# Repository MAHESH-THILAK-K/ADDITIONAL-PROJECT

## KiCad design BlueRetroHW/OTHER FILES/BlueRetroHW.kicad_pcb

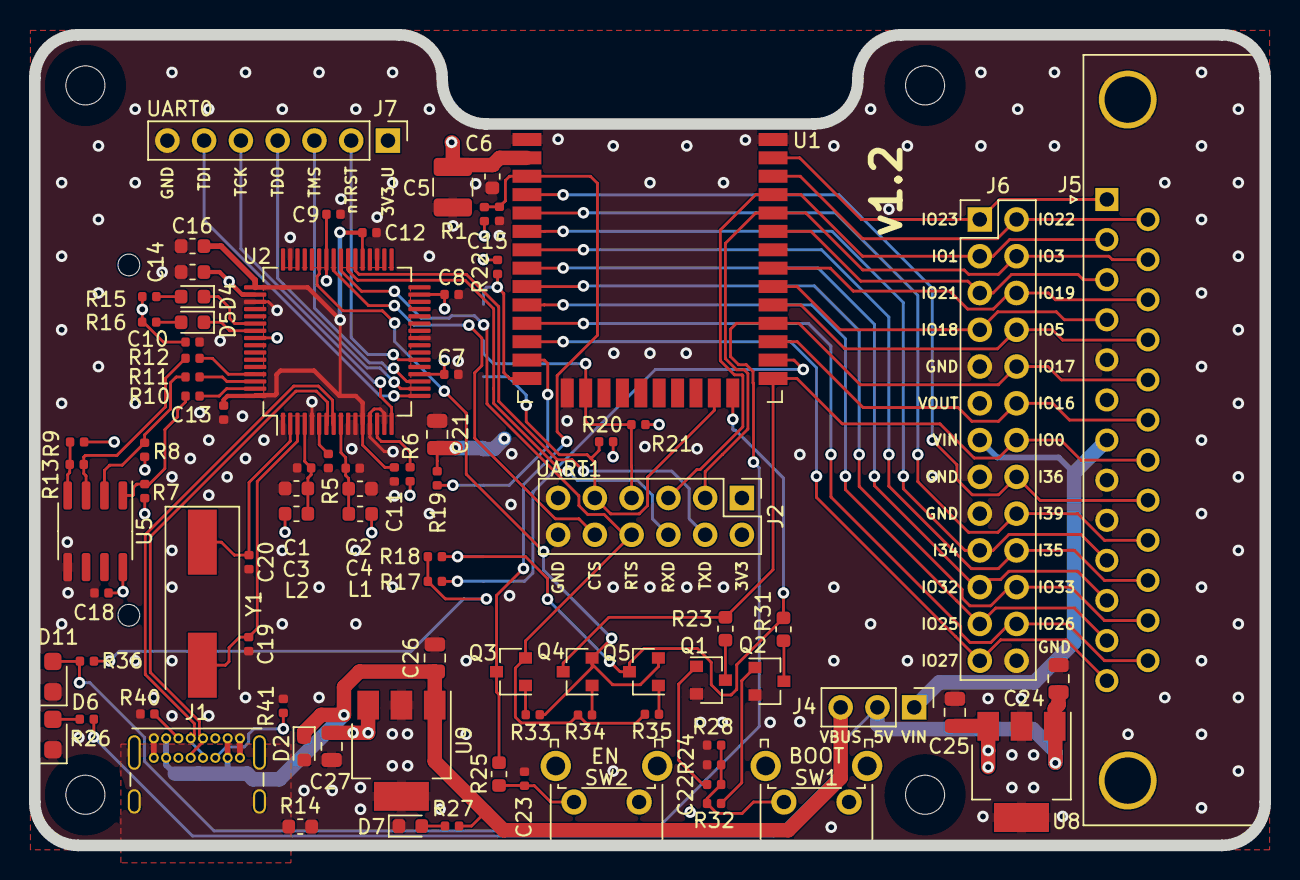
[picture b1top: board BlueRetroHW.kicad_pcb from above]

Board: 4 copper layers, 85.0 x 56.0 mm, 91 parts (1 on the bottom side), 77 nets.

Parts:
C1, C2, C7, C8, C9, C10, C11, C12, C13, C15, C18: 0.1u; C_0402_1005Metric
C3, C4, C14, C16: 4.7u; C_0603_1608Metric
C5: 100u; C_1210_3225Metric
C6: 1u; C_0603_1608Metric
C19, C20: 27p; C_0402_1005Metric
C21, C24, C25, C26, C27: 10u; C_0805_2012Metric
C22, C23: 1000p; C_0402_1005Metric
D2: ESDA25P35-1U1M; D_0603_1608Metric
D4: GREEN; LED_0603_1608Metric
D5, D7: RED; LED_0603_1608Metric
D6: GREEN_RA; LED_0605_1611Metric
D11: RED_RA; LED_0605_1611Metric
H1, H2, H3, H4: MountingHole; MountingHole_2.7mm_M2.5
J1: USB_C_Receptacle_USB2.0; USB_C_Receptacle_GCT_USB4085
J2: Conn_02x06; PinHeader_2x06_P2.54mm_Vertical
J3: SD_Card; SD_Kyocera_145638009511859+
J4: Conn_01x03; PinHeader_1x03_P2.54mm_Vertical
J5: DB25_Female; DSUB-25_Female_Horizontal_P2.77x2.84mm_EdgePinOffset8.1mm_H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
J6: Conn_02x13; PinHeader_2x13_P2.54mm_Vertical_TB
J7: Conn_01x07; PinHeader_1x07_P2.54mm_Vertical
L1, L2: 1K@100MHz; L_0603_1608Metric
Q1, Q2: BSS138; SOT-23
Q3, Q4, Q5: S8050; SOT-23
R1, R5: 12K; R_0402_1005Metric
R6, R24, R32: 1K; R_0402_1005Metric
R7, R8, R9, R17, R18, R19, R20, R21, R22, R28: 10K; R_0402_1005Metric
R10, R11, R12: 33; R_0402_1005Metric
R13: 2.2K; R_0402_1005Metric
R14, R23, R25, R31: 0; R_0603_1608Metric
R15, R16, R36: 64.9; R_0402_1005Metric
R26, R27: 150; R_0402_1005Metric
R33, R34, R35: 100K; R_0402_1005Metric
R40, R41: 5.1K; R_0402_1005Metric
SW1: BOOT; SW_Tactile_SPST_Angled_PTS645Vx83-2LFS
SW2: EN; SW_Tactile_SPST_Angled_PTS645Vx83-2LFS
U1: ESP32-WROOM-32E; ESP32-WROOM-32
U2: FT2232HL; LQFP-64_10x10mm_P0.5mm
U5: M93C46; SOIC-8_3.9x4.9mm_P1.27mm
U8, U9: AP7361C-33E; SOT-223-3_TabPin2
Y1: 12MHz; Crystal_SMD_HC49-SD

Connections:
+1V8: C11.1, C12.1, C13.1, C16.1, U2.12, U2.37, U2.49, U2.64
+3V3: C5.1, C6.1, C21.1, C25.1, J2.1, J2.2, J3.4, J5.6, J6.6, R1.1, R17.1, R18.1, R19.1, R20.1, R21.1, R22.1, R36.1, SW1.1, U1.2, U8.3
+3V3_USB: C7.1, C8.1, C9.1, C10.1, C14.1, C18.1, C27.1, J7.1, L1.2, L2.2, R6.1, R7.2, R8.2, R9.2, R15.2, R16.2, U2.20, U2.31, U2.42, U2.50, U2.56, U5.8, U9.3
+5V: C24.1, J4.2, R26.1, U8.1
/EN: C15.1, Q3.3, R1.2, R25.1, U1.3
/I34: J5.10, J6.10, U1.6
/I35: J5.23, J6.23, U1.7
/I36: J5.21, J6.21, U1.4
/I39: J5.22, J6.22, U1.5
/IO0: J5.20, J6.20, Q4.3, R23.1, U1.25
/IO1: J2.5, J5.2, J6.2, U1.35
/IO2: J3.7, Q5.3, R18.2, R31.1, U1.24
/IO3: J2.3, J5.15, J6.15, U1.34
/IO4: J3.8, R17.2, U1.26
/IO5: J5.17, J6.17, U1.29
/IO12: J3.9, R22.2, U1.14
/IO13: J2.7, J3.1, R21.2, U1.16
/IO14: J3.5, R19.2, U1.13
/IO15: J2.9, J3.2, R20.2, U1.23
/IO16: J5.19, J6.19, U1.27
/IO17: D11.2, J5.18, J6.18, R36.2, U1.28
/IO18: J5.4, J6.4, U1.30
/IO19: J5.16, J6.16, U1.31
/IO21: J5.3, J6.3, U1.33
/IO22: J5.14, J6.14, U1.36
/IO23: J5.1, J6.1, U1.37
/IO25: J5.12, J6.12, U1.10
/IO26: J5.25, J6.25, U1.11
/IO27: J5.13, J6.13, U1.12
/IO32: J5.11, J6.11, U1.8
/IO33: J5.24, J6.24, U1.9
/RXD: J2.6, U2.39
/TCK: J7.5, U2.16
/TDI: J7.6, U2.17
/TDO: J7.4, U2.18
/TMS: J7.3, U2.19
/TXD: J2.4, U2.38
/USB_C_N: J1.A7, J1.B7, U2.7
/USB_C_P: J1.A6, J1.B6, U2.8
/nCTS: J2.10, U2.41
/nDTR: Q4.2, Q5.2, R33.2, U2.43
/nRTS: J2.8, Q3.2, R34.2, R35.2, U2.40
/nTRST: J7.2, U2.22
GND: C1.2, C2.2, C3.2, C4.2, C5.2, C6.2, C7.2, C8.2, C9.2, C10.2, C11.2, C12.2, C13.2, C14.2, C15.2, C16.2, C18.2, C19.2, C20.2, C21.2, C22.2, C23.2, C24.2, C25.2, C26.2, C27.2, D2.2, D6.1, D7.1, D11.1, J1.A1, J1.A12, J1.B1, J1.B12, J2.11, J2.12, J3.3, J3.6, J3.12, J3.13, J5.0, J5.5, J5.8, J5.9, J6.5, J6.8, J6.9, J6.26, J7.7, Q1.2, Q2.2, R5.1, R14.2, R28.2, R40.1, R41.1, SW2.1, U1.1, U1.15, U1.38, U2.1, U2.5, U2.10, U2.11, U2.13, U2.15, U2.25, U2.35, U2.47, U2.51, U5.5, U8.2, U9.2
unnamed: C1.1, C3.1, L2.1, U2.4
unnamed: C2.1, C4.1, L1.1, U2.9
unnamed: C19.1, U2.3, Y1.2
unnamed: C20.1, U2.2, Y1.1
unnamed: C22.1, R24.2, R28.1, R32.2, SW1.2
unnamed: C23.1, R25.2, SW2.2
unnamed: D4.1, U2.54
unnamed: D4.2, R15.1
unnamed: D5.1, U2.55
unnamed: D5.2, R16.1
unnamed: D6.2, R26.2
unnamed: D7.2, R27.2
unnamed: J1.A5, R40.2
unnamed: J1.B5, R41.2
unnamed: J1.S1, R14.1
unnamed: Q1.1, R24.1
unnamed: Q1.3, R23.2
unnamed: Q2.1, R32.1
unnamed: Q2.3, R31.2
unnamed: Q3.1, R33.1
unnamed: Q4.1, R34.1
unnamed: Q5.1, R35.1
unnamed: R5.2, U2.6
unnamed: R6.2, U2.14
unnamed: R7.1, R10.1, U5.1
unnamed: R10.2, U2.63
unnamed: R8.1, R11.1, U5.2
unnamed: R11.2, U2.62
unnamed: R12.1, R13.2, U5.3
unnamed: R12.2, U2.61
unnamed: R9.1, R13.1, U5.4
VBUS: C26.1, D2.1, J1.A4, J1.A9, J1.B4, J1.B9, J4.3, R27.1, U9.1
VIN: J4.1, J5.7, J6.7

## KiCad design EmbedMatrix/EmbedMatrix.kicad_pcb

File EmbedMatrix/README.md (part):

<div align="center">

<br/>

```
███████╗███╗   ███╗██████╗ ███████╗██████╗ ███╗   ███╗ █████╗ ████████╗██████╗ ██╗██╗  ██╗
██╔════╝████╗ ████║██╔══██╗██╔════╝██╔══██╗████╗ ████║██╔══██╗╚══██╔══╝██╔══██╗██║╚██╗██╔╝
█████╗  ██╔████╔██║██████╔╝█████╗  ██║  ██║██╔████╔██║███████║   ██║   ██████╔╝██║ ╚███╔╝ 
██╔══╝  ██║╚██╔╝██║██╔══██╗██╔══╝  ██║  ██║██║╚██╔╝██║██╔══██║   ██║   ██╔══██╗██║ ██╔██╗ 
███████╗██║ ╚═╝ ██║██████╔╝███████╗██████╔╝██║ ╚═╝ ██║██║  ██║   ██║   ██║  ██║██║██╔╝ ██╗
╚══════╝╚═╝     ╚═╝╚═════╝ ╚══════╝╚═════╝ ╚═╝     ╚═╝╚═╝  ╚═╝   ╚═╝   ╚═╝  ╚═╝╚═╝╚═╝  ╚═╝
```

<h3>🔗 Modular Embedded Matrix Platform for Multi-Node Sensing & Control</h3>
<h4><i>Connect everything. Scale infinitely. Deploy anywhere.</i></h4>

<br/>

<br/>

---

**[📡 Overview](#-overview) · [✨ Features](#-features) · [🔩 Architecture](#-system-architecture) · [📐 Matrix Topology](#-matrix-topology) · [📦 BOM](#-bill-of-materials) · [🚀 Quickstart](#-quickstart) · [📁 File Tree](#-file-tree) · [🗺 Roadmap](#-roadmap) · [🤝 Contribute](#-contributing)**

---

</div>

<br/>

## 📡 Overview

**EmbedMatrix** is a scalable, modular embedded matrix platform designed for distributed sensing, multi-node control, and mesh-capable IoT deployments. Built around the **STM32F031K6T6** ARM Cortex-M0+ MCU, each EmbedMatrix node is a self-contained, hot-swappable unit that snaps into a shared backplane bus — enabling you to build sensor grids, actuator arrays, and telemetry networks from 1 node to 64 nodes without redesigning hardware.

Every node carries its own processing, communication, and power regulation, while the backplane provides a unified interconnect mesh of **I²C, SPI, and UART** buses with automatic address arbitration. Whether you're building a 4-node motor controller, a 16-node environmental sensor grid, or a 64-node LED matrix display, EmbedMatrix scales linearly — just add nodes.

```
EmbedMatrix Design Philosophy
───────────────────────────────────
  → Hot-swappable node architecture      (snap-in / snap-out, no reboot)
  → Unified backplane bus matrix         (I²C + SPI + UART shared lanes)
  → Auto-address arbitration             (DIP switch / EEPROM ID per node)
  → Self-contained per-node power        (LDO + ferrite, no bus droop)
  → Crystal-locked sync across nodes     (HSE 8 MHz, PLL 48 MHz)
  → ESD-protected edge connectors        (TVS diodes on all bus lines)
  → Fabrication-ready from day one       (JLCPCB / PCBWay Gerber-clean)
```

<br/>

---

## ✨ Features

<br/>

<table>
<tr>
<td width="50%">

### 🔗 Matrix & Bus Architecture
- **Hot-swappable node slots** — add/remove nodes live, no system reset
- **Unified backplane bus** — I²C (400 kHz), SPI (24 Mbit/s), UART (115200) shared
- **Auto-address arbitration** — 6-bit DIP switch or EEPROM-stored node ID
- **Bus isolation per node** — PCA9548 I²C mux + SPI chip-select matrix
- **ESD protection** — TVS diode arrays on all backplane edge connectors
- **Status LED matrix** — per-node RGB status, backplane health indicator

</td>
<td width="50%">

### 🧠 Processing & Control
- **ARM Cortex-M0+** @ 48 MHz per node (0.95 DMIPS/MHz)
- **32 KB Flash** — distributed firmware, mesh protocol stack
- **4 KB SRAM** — runtime buffers, bus arbitration tables
- **12-bit ADC** — 10 channels per node for sensor aggregation
- **9-channel PWM** — synchronized motor / LED / servo control
- **Hardware multiplier** — single-cycle 32×32 MAC for DSP tasks

</td>
</tr>
<tr>
<td width="50%">

### ⚡ Power & Reliability
- **Per-node LDO 3.3V** — AMS1117-3.3 with ferrite bead isolation
- **Bulk capacitor reservoir** — 10µF per node, 100µF on backplane
- **Brown-out reset (BOR)** — per-node voltage monitoring
- **Independent watchdog (IWDG)** — node-level crash recovery
- **Low-power modes** — Sleep, Stop, Standby (< 10 µA standby)

</td>
<td width="50%">

### 📡 Communication & Sync
- **USART1** — inter-node messaging, debug console, AT commands
- **SPI1** — high-speed sensor / flash / display peripheral bus
- **I²C1** — multi-drop sensor network, EEPROM config storage
- **SWD debug** — 2-wire programming per node via backplane
- **Sync line** — dedicated hardware sync for PWM phase-lock across nodes

</td>
</tr>
</table>

<br/>

---

## 🔩 System Architecture

```
╔═══════════════════════════════════════════════════════════════════════════╗
║                    EmbedMatrix — Full System Block Diagram               ║
╠═══════════════════════════════════════════════════════════════════════════╣
║                                                                           ║
║   ══════════════════════════ Backplane Bus Matrix ══════════════════════  ║
║                                                                           ║
║   ┌─────────────────────────────────────────────────────────────────────┐ ║
║   │  BUS_I²C_SCL  │  BUS_I²C_SDA  │  BUS_SPI_SCK  │  BUS_SPI_MOSI    │ ║
║   │  BUS_SPI_MISO │  BUS_UART_TX  │  BUS_UART_RX  │  BUS_SYNC_CLK    │ ║
║   │  BUS_VCC_3V3  │  BUS_VCC_5V   │  BUS_GND      │  BUS_NRST_MATRIX │ ║
║   └─────────────────────────────────────────────────────────────────────┘ ║
║                                    │                                      ║
║         ┌──────────┬──────────┬────┴────┬──────────┬──────────┐           ║
║         ▼          ▼          ▼         ▼          ▼          ▼           ║
║   ┌─────────┐ ┌─────────┐ ┌─────────┐ ┌─────────┐ ┌─────────┐ ┌─────────┐║
║   │ Node 00 │ │ Node 01 │ │ Node 02 │ │ Node 03 │ │  ...    │ │ Node 63 │║
║   │ ID=0x00 │ │ ID=0x01 │ │ ID=0x02 │ │ ID=0x03 │ │         │ │ ID=0x3F │║
║   └────┬────┘ └────┬────┘ └────┬────┘ └────┬────┘ └────┬────┘ └────┬────┘║
║        │           │           │           │           │           │      ║
║   ═════╧═══════════╧═══════════╧═══════════╧═══════════╧═══════════╧════  ║
║                                                                           ║
║   ════════════════════════ Single Node Internals ═══════════════════════  ║
║                                                                           ║
║   ┌─────────────────────────────────────────────────────────────────┐    ║
║   │              STM32F031K6T6 — ARM Cortex-M0+ Core               │    ║
║   │                                                                 │    ║
║   │   ┌─────────────┐  ┌─────────────┐  ┌─────────────────────┐   │    ║
║   │   │  32 KB Flash │  │   4 KB SRAM  │  │  NVIC + SysTick     │   │    ║
║   │   │  (0x08000000)│  │  (0x20000000)│  │  32 IRQ priorities  │   │    ║
║   │   └─────────────┘  └─────────────┘  └─────────────────────┘   │    ║
║   │                                                                 │    ║
║   │   ┌─────────────┐  ┌─────────────┐  ┌─────────────────────┐   │    ║
║   │   │   RCC/PLL   │  │    PWR/BOR   │  │   Bus Arbiter (SW)  │   │    ║
║   │   │  48 MHz SYS │  │   LDO 1.8V   │  │   Node ID register  │   │    ║
║   │   └─────────────┘  └─────────────┘  └─────────────────────┘   │    ║
║   └────────────────────────┬──────────────────────────────────────┘    ║
║                            │                                           ║
║   ════════════════════════ Peripherals ═══════════════════════════════  ║
║                            │                                           ║
║   ┌──────────┐ ┌──────────┐ ┌──────────┐ ┌──────────┐ ┌──────────┐   ║
║   │  USART1  │ │  SPI1    │ │  I²C1    │ │  TIM1/2  │ │  ADC1    │   ║
║   │ PA9/PA10 │ │ PA5-PA7  │ │ PA9/PA10 │ │ PA0-PA3  │ │ PA0-PA7  │   ║
║   │ 115200   │ │ 24 Mbit  │ │ 400 kHz  │ │  PWM     │ │ 12-bit   │   ║
║   └──────────┘ └──────────┘ └──────────┘ └──────────┘ └──────────┘   ║
║                            │                                           ║
║   ════════════════════════ Node Interface ══════════════════════════  ║
║                            │                                           ║
║        ┌───────────────────┴───────────────────┐                       ║
║        ▼                                       ▼                       ║
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
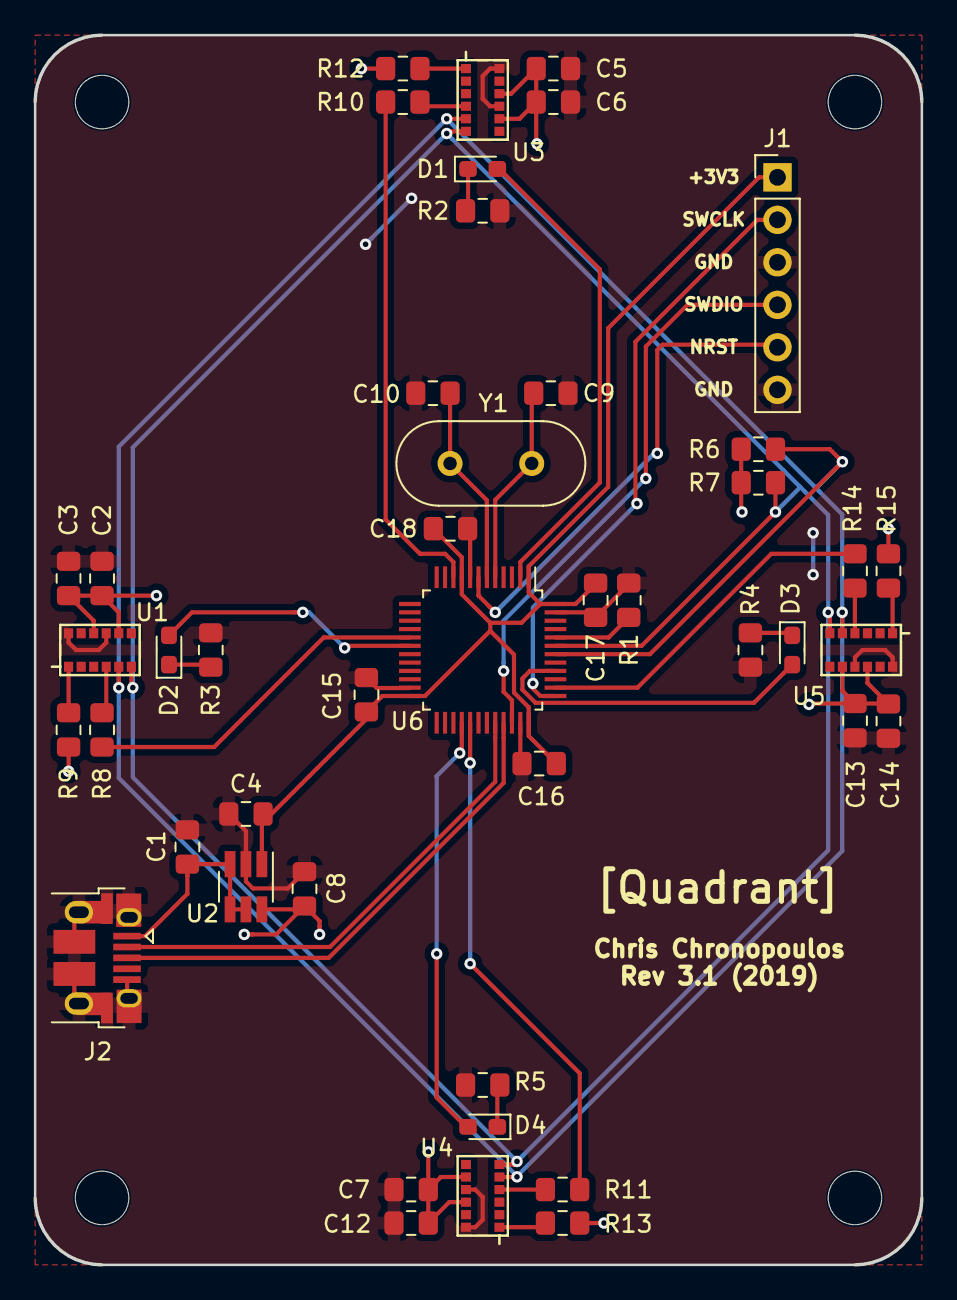
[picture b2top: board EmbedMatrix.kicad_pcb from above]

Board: 2 copper layers, 53.0 x 73.5 mm, 45 parts (0 on the bottom side), 34 nets.

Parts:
C1, C4, C8: 1uF; C_0805_2012Metric_Pad1.15x1.40mm_HandSolder
C2, C5, C7, C13: 4.7uF; C_0805_2012Metric_Pad1.15x1.40mm_HandSolder
C3, C6, C12, C14: 0.1uF; C_0805_2012Metric_Pad1.15x1.40mm_HandSolder
C9, C10: 18 pF; C_0805_2012Metric_Pad1.15x1.40mm_HandSolder
C15, C16, C17, C18: 0.1 uF; C_0805_2012Metric_Pad1.15x1.40mm_HandSolder
D1, D2, D3, D4: LED; LED_0603_1608Metric_Pad1.05x0.95mm_HandSolder
J1: Conn_01x06; PinHeader_1x06_P2.54mm_Vertical
J2: USB_B_Micro; USB_Micro-B_Amphenol_10103594-0001LF_Horizontal
R1: 10k; R_0805_2012Metric_Pad1.15x1.40mm_HandSolder
R2, R3, R4, R5: 10; R_0805_2012Metric_Pad1.15x1.40mm_HandSolder
R6, R7: 4.7k; R_0805_2012Metric_Pad1.15x1.40mm_HandSolder
R8, R9, R10, R11, R12, R13, R14, R15: 47k; R_0805_2012Metric_Pad1.15x1.40mm_HandSolder
U1, U3, U4, U5: VL6180X
U2: AP7332-2833; SOT-23-6_Handsoldering
U6: STM32F070CBTx; LQFP-48_7x7mm_P0.5mm
Y1: 8 MHz; Crystal_HC49-U_Vertical

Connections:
+2V8: C2.2, C3.2, C5.2, C6.2, C7.2, C8.1, C12.2, C13.2, C14.2, R6.1, R7.1, R9.1, R12.1, R13.1, R15.1, U1.8, U1.10, U2.6, U3.8, U3.10, U4.8, U4.10, U5.8, U5.10
+3V3: C4.1, C15.2, C16.2, C17.2, C18.2, J1.1, U2.1, U6.1, U6.9, U6.24, U6.36, U6.48
EN1: R10.1, U6.10
EN2: R14.1, U6.38
EN3: R11.1, U6.29
EN4: R8.1, U6.17
GND: C1.2, C2.1, C3.1, C4.2, C5.1, C6.1, C7.1, C8.2, C9.2, C10.2, C12.1, C13.1, C14.1, C15.1, C16.1, C17.1, C18.1, J1.3, J1.6, J2.5, J2.6, R1.1, R2.1, R3.1, R4.1, R5.1, U1.9, U1.12, U2.2, U3.9, U3.12, U4.9, U4.12, U5.9, U5.12, U6.8, U6.23, U6.35, U6.47
NRST: J1.5, U6.7
unnamed: C9.1, U6.5, Y1.1
unnamed: C10.1, U6.6, Y1.2
unnamed: D1.1, R2.2
unnamed: D1.2, U6.2
unnamed: D2.1, R3.2
unnamed: D2.2, U6.18
unnamed: D3.1, R4.2
unnamed: D3.2, U6.40
unnamed: D4.1, R5.2
unnamed: D4.2, U6.28
unnamed: R1.2, U6.44
unnamed: R8.2, U1.4
unnamed: R9.2, U1.1
unnamed: R10.2, U3.4
unnamed: R11.2, U4.4
unnamed: R12.2, U3.1
unnamed: R13.2, U4.1
unnamed: R14.2, U5.4
unnamed: R15.2, U5.1
SCL: R6.2, U1.5, U3.5, U4.5, U5.5, U6.42
SDA: R7.2, U1.6, U3.6, U4.6, U5.6, U6.43
SWCLK: J1.2, U6.37
SWDIO: J1.4, U6.34
USB5V: C1.1, J2.1, U2.3, U2.4, U2.5
USBDM: J2.2, U6.32
USBDP: J2.3, U6.33

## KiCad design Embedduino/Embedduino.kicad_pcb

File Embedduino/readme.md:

# 🚀 Embedduino

> ⚡ Compact Arduino-compatible SMD development board for embedded systems & IoT.

---

## 📌 About

**Embedduino** is a custom-designed development board based on the **ATmega328P-AU**, integrating power regulation, communication interfaces, and onboard peripherals into a compact PCB.

It is built to bridge the gap between **Arduino prototyping and real hardware design**.

---

## ✨ Features

* ATmega328P-AU (Arduino UNO compatible)
* 16 MHz Crystal Oscillator
* USB Type-C (5V input)
* 12V Barrel Jack support
* Dual LDO (12V → 5V → 3.3V)
* Bluetooth support (HC-05 / HC-06)
* RGB LED + Status LEDs
* Onboard Buzzer
* ICSP Programming Header
* Full GPIO breakout (D0–D13, A0–A5)

---

## 🧩 Components

| Component     | Description               |
| ------------- | ------------------------- |
| ATmega328P-AU | Microcontroller           |
| TLV76750      | 12V → 5V Regulator        |
| AMS1117-3.3V  | 5V → 3.3V Regulator       |
| WS2812B       | Addressable RGB LED       |
| HC-05         | Bluetooth Module          |
| APDS-9960     | Gesture Sensor (optional) |
| USB-C         | Power Input               |
| Barrel Jack   | 12V Input                 |
| ICSP          | Programming Header        |
| Buzzer        | Audio Output              |

---

## ⚙️ Specifications

* **MCU:** ATmega328P-AU
* **Clock:** 16 MHz
* **Voltage:** 5V / 12V
* **Logic Levels:** 5V / 3.3V
* **Communication:** UART
* **PCB:** 2 Layer

---

## 🚀 Getting Started

**Bootloader**

* Flash using ICSP programmer

**Upload Code**

* Use FTDI / USB-UART
* Select **Arduino UNO** in Arduino IDE

**Power Options**

* USB-C (5V)
* Barrel Jack (12V)

---

## 🔌 Pinout

| Type    | Pins            |
| ------- | --------------- |
| Digital | D0–D13          |
| Analog  | A0–A5           |
| UART    | TX / RX         |
| Power   | 5V / 3.3V / GND |

---

## ⚠️ Note

> DRC is not fully resolved — verify before fabrication.

---
## 🧪 Use Cases

* Robotics
* IoT Projects
* Wireless Systems
* Embedded Learning

---

## 🛠️ Roadmap

* [ ] Fix DRC issues
* [ ] Add USB-UART IC
* [ ] Improve power efficiency
* [ ] Hardware testing

---

## 👨‍💻 Author

**Mahesh Thilak**
🔗 https://github.com/MAATHES-THILAK-K

---

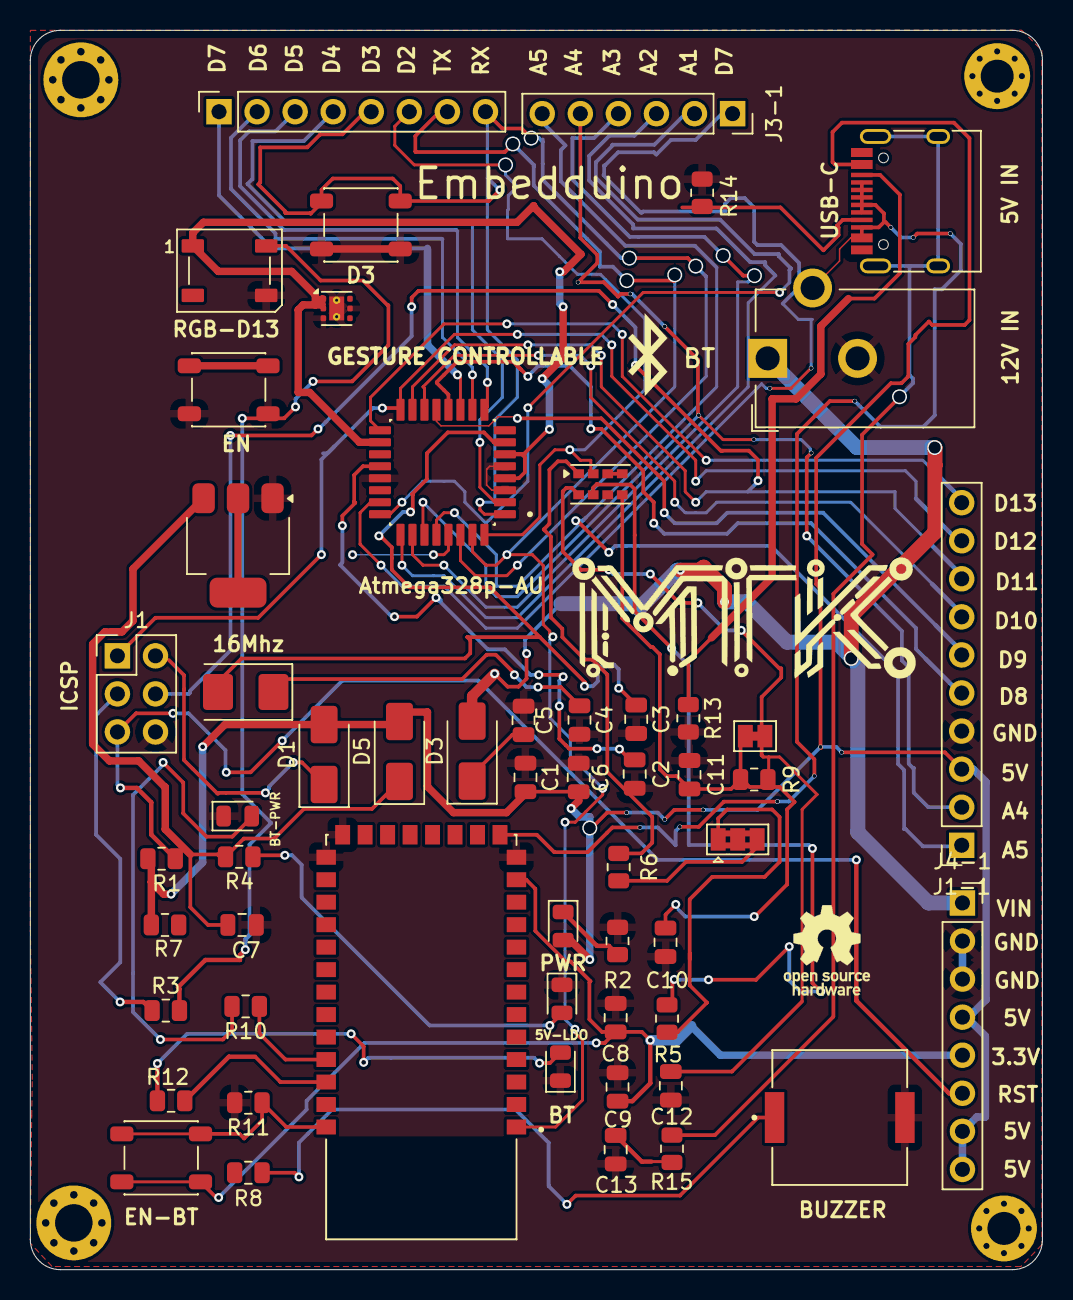
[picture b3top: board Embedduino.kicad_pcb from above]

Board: 2 copper layers, 67.5 x 82.7 mm, 57 parts (0 on the bottom side), 51 nets.

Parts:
5V-LDO: LED; LED_0805_2012Metric
12V IN: Barrel_Jack; BarrelJack_CUI_PJ-102AH_Horizontal
16Mhz: Crystal; Crystal_SMD_5032-2Pin_5.0x3.2mm
BT: LED; LED_0805_2012Metric
BT-PWR: LED; LED_0805_2012Metric
BZ1: Buzzer; SPKR_PKMCS0909E4000-R1
C1, C2, C13: 100nf; C_0805_2012Metric
C3, C4: 22pf; C_0805_2012Metric
C5: 1uf; C_0805_2012Metric
C6: 2.2uf; C_0805_2012Metric
C7, C8: 10uf; C_0805_2012Metric
C9: 0.1uf; C_0805_2012Metric
C10: 1.0uf; C_0805_2012Metric
C11: 100uf; C_0805_2012Metric
C12: 1.0fu; C_0805_2012Metric
D1, D3#2, D5: SS14; D_SMA
D3: SW_DPST_x2; SW_SPST_PTS647_Sx50
EN: SW_DPST_x2; SW_SPST_PTS647_Sx50
EN-BT: SW_DPST_x2; SW_SPST_PTS647_Sx50
H1, H2: MountingHole; MountingHole_2.2mm_M2_Pad_Via
J1: ICSP; PinHeader_2x03_P2.54mm_Vertical
J1-1: Conn_01x10_Pin; PinSocket_1x10_P2.54mm_Vertical
J2-1, J4-1: Conn_01x08_Pin; PinSocket_1x08_P2.54mm_Vertical
J3-1: Conn_01x06_Pin; PinSocket_1x06_P2.54mm_Vertical
JP1: SolderJumper_3_Bridged123; SolderJumper-3_P1.3mm_Bridged2Bar123_Pad1.0x1.5mm
JP2: SolderJumper_2_Bridged; SolderJumper-2_P1.3mm_Bridged_Pad1.0x1.5mm
PWR: LED; LED_0805_2012Metric
R1, R7, R11: 10k; R_0805_2012Metric
R2, R12: 1k; R_0805_2012Metric
R3: 330; R_0805_2012Metric
R4: 2.2k; R_0805_2012Metric
R5, R6: 4.7k; R_0805_2012Metric
R8: 100; R_0805_2012Metric
R9: DNP; R_0805_2012Metric
R10: 2k; R_0805_2012Metric
R13, R14: 5.1k; R_0805_2012Metric
R15: 1M; R_0805_2012Metric
RGB-D13: WS2812B; LED_WS2812B_PLCC4_5.0x5.0mm_P3.2mm
U1: ATMEGA328P-AU; QFP80P900X900X120-32N
U2: TLV76750DRVx; WSON-6-1EP_2x2mm_P0.65mm_EP1x1.6mm_ThermalVias
U3: AMS1117-3.3; SOT-223-3_TabPin2
U4: APDS-9960; Avago_APDS-9960
U5: HC-05; XCVR_HC-05
USB-C: USB_C_Receptacle_PowerOnly_6P; USB_C_Receptacle_HRO_TYPE-C-31-M-12

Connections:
3.3v: C8.1, C9.1, EN-BT.2 (B), J4-1.5, U3.2 (VO), U5.12 (3.3_VCC)
5V: C1.2, C6.1, D1.2 (A), D5.2 (A), J1-1.3, J4-1.4, J4-1.7, J4-1.8, PWR.2 (A), R1.2, R7.1, RGB-D13.1 (VDD), U1.4 (VCC), U1.6 (VCC__1), U1.18 (AVCC), U2.1 (OUT), U2.2 (SNS), USB-C.A9 (VBUS), USB-C.B9 (VBUS)
A0: J3-1.1, U1.23 (PC0)
A1: J3-1.2, U1.24 (PC1)
A2: J3-1.3, U1.25 (PC2)
A3: J3-1.4, U1.26 (PC3)
A4: J1-1.2, J3-1.5, U1.27 (PC4)
A5: J1-1.1, J3-1.6, U1.28 (PC5)
D2: J2-1.6, R7.2, U1.32 (PD2), U4.2 (INT)
D3: D3.1 (A), J2-1.5, U1.1 (PD3)
D4: J2-1.4, U1.2 (PD4)
D5: J2-1.3, U1.9 (PD5)
D6: J2-1.2, R8.1, U1.10 (PD6)
D7: J2-1.1, U1.11 (PD7)
D8: J1-1.5, U1.12 (PB0)
D9: J1-1.6, U1.13 (PB1)
D10: J1-1.7, U1.14 (PB2)
D11: J1.4, J1-1.8, U1.15 (PB3)
D12: J1.1, J1-1.9, U1.16 (PB4)
D13: J1.3, J1-1.10, R3.1, U1.17 (PB5)
GND: 5V-LDO.1 (K), 12V IN.2, BT.1 (K), BT-PWR.1 (K), BZ1.2 (-), C1.1, C2.2, C3.2, C4.2, C5.2, C6.2, C7.2, C8.2, C9.2, C10.1, C11.2, C12.2, C13.2, D3.2 (B), EN.2 (B), J1.6, J1-1.4, J4-1.2, J4-1.3, R2.1, R11.2, R13.2, R14.2, RGB-D13.3 (VSS), U1.3 (GND), U1.5 (GND__1), U1.21 (GND__2), U2.3 (GND), U2.5 (GND), U2.7 (PAD), U3.1 (GND), U4.6 (GND), U5.13 (GND), U5.21 (GND), U5.22 (GND), USB-C.A12 (GND), USB-C.B12 (GND)
unnamed: BZ1.1 (+), R8.2
unnamed: C13.1, R15.2
unnamed: D1.1 (K), J1.2
unnamed: PWR.1 (K), R2.2
unnamed: C5.1, D3#2.1 (K), U2.4 (EN), U2.6 (IN)
unnamed: R3.2, RGB-D13.4 (DIN)
unnamed: C7.1, D5.1 (K), R4.1, U3.3 (VI)
unnamed: 5V-LDO.2 (A), R4.2
unnamed: BT-PWR.2 (A), R10.2
unnamed: BT.2 (A), R12.1
unnamed: R14.1, USB-C.A5 (CC1)
unnamed: R13.1, USB-C.B5 (CC2)
unnamed: R15.1, USB-C.S1 (SHIELD)
unnamed: JP1.1 (A), R5.1
unnamed: JP1.3 (B), R6.1
unnamed: C12.1, JP2.2 (B), R9.1, U4.8 (VDD)
unnamed: EN-BT.1 (A), R11.1, U5.34 (PIO[11])
unnamed: C2.1, U1.20 (AREF)
unnamed: U4.3 (LDR), U4.4 (LED_K)
unnamed: R10.1, U5.31 (PIO[8])
PB6: 16Mhz.2, C3.1, U1.7 (PB6)
PB7: 16Mhz.1, C4.1, U1.8 (PB7)
RST: EN.1 (A), J1.5, J4-1.6, R1.1, U1.29 (PC6/~RESET)
RX: J2-1.8, U1.30 (PD0), U5.2 (UART-RX)
SCL: R5.2, U4.7 (SCL)
SDA: R6.2, U4.1 (SDA)
STATE: R12.2, U5.32 (PIO[9])
TX: J2-1.7, U1.31 (PD1), U5.1 (UART-TX)
Vin: 12V IN.1, D3#2.2 (A), J4-1.1
Vl: C10.2, C11.1, JP2.1 (A), R9.2, U4.5 (LED_A)

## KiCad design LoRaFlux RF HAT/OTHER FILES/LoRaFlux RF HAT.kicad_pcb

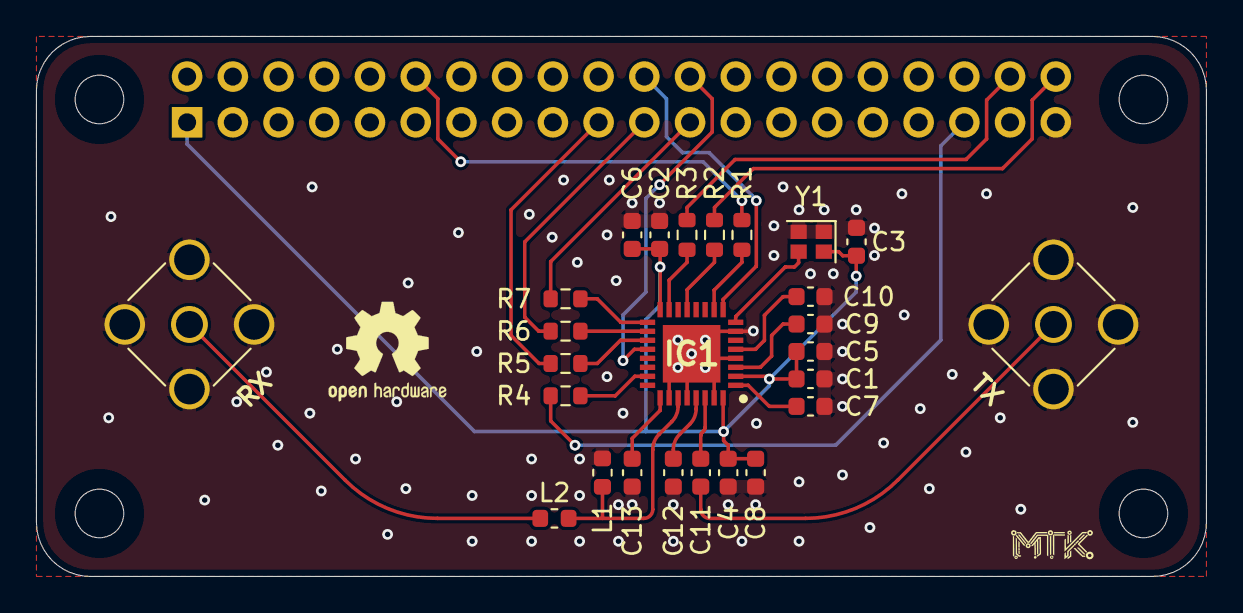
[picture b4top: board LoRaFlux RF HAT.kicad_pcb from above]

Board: 2 copper layers, 65.0 x 30.0 mm, 32 parts (1 on the bottom side), 28 nets.

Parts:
C1, C2, C3, C4: 10n; C_0603_1608Metric
C5, C6, C7, C8, C9, C10, C13: 100n; C_0603_1608Metric
C11: 33p; C_0603_1608Metric
C12: 27p; C_0603_1608Metric
H1, H2, H3, H4: MountingHole; MountingHole_2.7mm_M2.5_DIN965
IC1: SX1255; QFN50P500X500X80-33N-D
J1: TX_SMA; SMA_Amphenol_901-144_Vertical
J2: RX_SMA; SMA_Amphenol_901-144_Vertical
J3: RPi Zero; PinSocket_2x20_P2.54mm_Vertical
L1: 82n; L_0603_1608Metric
L2: 39n; L_0603_1608Metric
R1, R2, R3, R4, R5, R6, R7: 100R; R_0603_1608Metric
SYM1: Logo_Open_Hardware_Small; OSHW-Logo2_7.3x6mm_SilkScreen
Y1: 32MHz; Crystal_SMD_2016-4Pin_2.0x1.6mm

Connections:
+3V3: C1.1, C2.1, C3.1, C4.1, C5.1, C6.1, C8.1, IC1.2 (VBATI), IC1.16 (VBAT2), IC1.32 (VBAT3), J3.1, Y1.4 (VDD)
/DIO2: J3.35, R4.1
/I_IN: J3.40, R2.2
/I_OUT: J3.38, R3.2
/MISO: J3.21, R6.1
/MOSI: J3.19, R5.1
/OUT: J3.12, R1.2
/RST: IC1.9 (RESET), J3.22
/SCK: J3.23, R7.1
/TCXO_CLK: IC1.8 (XTB), Y1.3 (OUT)
/~CS: IC1.20 (NSS), J3.24
GND: C1.2, C2.2, C3.2, C4.2, C5.2, C6.2, C7.2, C8.2, C9.2, C10.2, C12.2, C13.2, IC1.4 (GND_1), IC1.7 (GND_2), IC1.26 (GND_3), IC1.28 (GND_4), IC1.31 (GND_5), IC1.33 (GND_6), J1.2 (Ext), J2.2 (Ext), J3.39, L1.1, Y1.1 (Tri-State), Y1.2 (GND)
unnamed: IC1.10 (CK_OUT), R1.1
unnamed: IC1.23 (DIO2), R4.2
unnamed: IC1.13 (I_IN), R2.1
unnamed: IC1.15 (I_OUT), R3.1
unnamed: IC1.18 (MISO), R6.2
unnamed: IC1.19 (MOSI), R5.2
unnamed: IC1.27 (RFI), L1.2, L2.2
unnamed: C12.1, IC1.29 (RFO_N)
unnamed: C11.1, IC1.30 (RFO_P)
unnamed: IC1.17 (SCK), R7.2
unnamed: C13.1, IC1.25 (VR_ANA2)
unnamed: C9.1, IC1.3 (VR_ANAI)
unnamed: C10.1, IC1.5 (VR_DIG)
unnamed: C7.1, IC1.1 (VR_PA)
unnamed: C11.2, J1.1 (In)
unnamed: J2.1 (In), L2.1

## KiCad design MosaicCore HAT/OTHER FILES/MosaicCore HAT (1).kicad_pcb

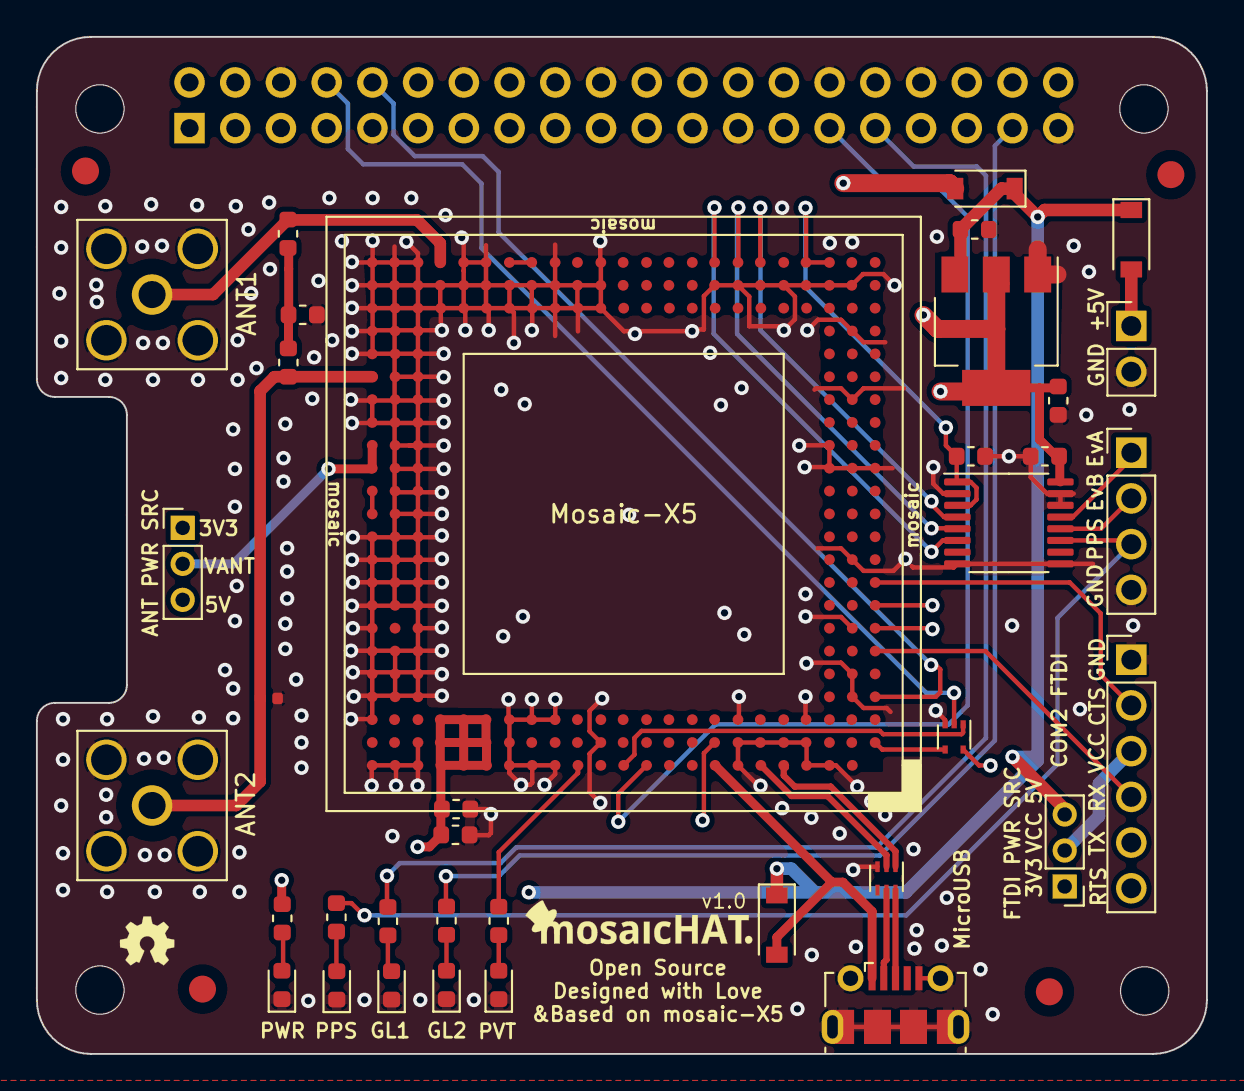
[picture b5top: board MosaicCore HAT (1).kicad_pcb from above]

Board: 4 copper layers, 65.0 x 56.5 mm, 41 parts (1 on the bottom side), 41 nets.

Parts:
C1, C3, C4, C5: 100nF; C_0603_1608Metric
C2, C6: 10uF; C_0603_1608Metric
C7: un-assembled; C_0603_1608Metric
D1, D2, D3: MBRX120LF-TP; D_SOD-123
D4, D5, D6, D7, D8: LED; LED_0603_1608Metric
D9: D_TVS; R_0402_1005Metric
FID1, FID2, FID3, FID4: Fiducial; Fiducial_1.5mm_Mask3mm
FL1: ECMF02-2AMX6; ST_UQFN-6L_1.5x1.7mm_Pitch0.5mm
J1, J2: Conn_Coaxial; SMA_Amphenol_132203-12_Horizontal
J3: USB_B_Micro; USB_Micro-B_Molex-105017-0001
J4: raspberrypi_hat_OX40HAT; PinSocket_2x20_P2.54mm_Vertical
J5: Conn_01x04_Male; PinHeader_1x04_P2.54mm_Vertical
J6: Conn_01x06_Male; PinHeader_1x06_P2.54mm_Vertical
J7: Conn_01x02_Male; PinHeader_1x02_P2.54mm_Vertical
JP1, JP2: Jumper_NC_Dual; PinHeader_1x03_P2.00mm_Vertical
L1, L2: 39nH; L_0603_1608Metric
R1, R2, R3, R4, R5: R330; R_0603_1608Metric
U1: mosaic-X5; mosaic_X5
U2: LD1117AS33TR; SOT-223
U3: SN74AVC4T245PW; TSSOP-16_4.4x5mm_P0.65mm
U4: SN74LVC1G126DRLR; SOT-553

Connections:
+1V8: C4.1, U1.AC3, U1.AC4, U3.1, U3.3
+3V3: C2.1, C5.1, C6.1, C7.1, JP1.1, JP2.1, R1.2, U1.A18, U1.A19, U1.A20, U1.B8, U1.B18, U1.B19, U1.B20, U1.C18, U1.C19, U1.C20, U2.2, U3.16, U4.5
+5V: C1.1, D1.1, D2.1, D3.1, JP1.3, JP2.3, U2.3
/2V8: U1.M23, U1.N23
/ANT1: J1.1, L1.1, U1.AC20
/ANT2: D9.2, J2.1, L2.2, U1.V23
/D+: FL1.6, J3.3
/D-: FL1.5, J3.2
/EVENTA_1V8: U1.AC6, U3.4
/EVENTA_3V3: J5.1, U3.13
/EVENTB_1V8: U1.AC7, U3.5
/EVENTB_3V3: J5.2, U3.12
/External_5V: D3.2, J7.1
/FTDI_PWR: J6.3, JP2.2
/GPLED: R5.2, U1.A14
/MODULE_RDY: U1.A12, U4.1
/MosaicCTS2: J6.2, U1.J1
/MosaicRTS2: J6.6, U1.G1
/MosaicRX1: J4.8, U4.2
/MosaicRX1_BufferOUT: U1.B1, U4.4
/MosaicRX2: J6.4, U1.F1
/MosaicTX1: J4.10, U1.D1
/MosaicTX2: J6.5, U1.H1
/PPSO_1V8: U1.AC8, U3.6
/PPSO_3V3: J5.3, R2.2, U3.11
/REF: U1.AC16, U1.AC17
/RPI_GP1: J4.31, R3.2
/RPI_GP2: J4.37, R4.2
/RPI_P5V: D2.2, J4.2, J4.4
/USB_N: FL1.2, U1.A6
/USB_P: FL1.1, U1.A5
/USB_V: D1.2, J3.1, U1.A8
/VANT: JP1.2, U1.P23, U1.R23
/nRST_IN: J4.29, U1.A11
GND: C1.2, C2.2, C3.2, C4.2, C5.2, C6.2, C7.2, D4.1, D5.1, D6.1, D7.1, D8.1, D9.1, FL1.3, J1.2, J2.2, J3.5, J3.6, J4.6, J4.9, J4.14, J4.20, J4.25, J4.30, J4.34, J4.39, J5.4, J6.1, J7.2, U1.A3, U1.A4, U1.A7, U1.A15, U1.A16, U1.A17, U1.A21, U1.A22, U1.A23, U1.AA13, U1.AA14, U1.AA15, U1.AA16, U1.AA17, U1.AA18, U1.AA19, U1.AA20, U1.AA21, U1.AA22, U1.AA23, U1.AB2, U1.AB3, U1.AB4, U1.AB5, U1.AB6, U1.AB7, U1.AB8, U1.AB13, U1.AB14, U1.AB15, U1.AB16, U1.AB17, U1.AB18, U1.AB19, U1.AB20, U1.AB21, U1.AB22, U1.AB23, U1.AC13, U1.AC15, U1.AC18, U1.AC19, U1.AC21, U1.AC22, U1.AC23, U1.B4, U1.B5, U1.B6, U1.B7, U1.B13, U1.B17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
unnamed: C3.1, L1.2, L2.1
unnamed: D4.2, R1.1
unnamed: D5.2, R2.1
unnamed: D6.2, R3.1
unnamed: D7.2, R4.1
unnamed: D8.2, R5.1

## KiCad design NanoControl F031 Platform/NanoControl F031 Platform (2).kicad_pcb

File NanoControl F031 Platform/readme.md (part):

<div align="center">

<br/>

```
███╗   ██╗ █████╗ ███╗   ██╗ ██████╗  ██████╗ ██████╗ ████████╗██████╗  ██████╗ ██╗
████╗  ██║██╔══██╗████╗  ██║██╔═══██╗██╔════╝ ██╔══██╗╚══██╔══╝██╔══██╗██╔═══██╗██║
██╔██╗ ██║███████║██╔██╗ ██║██║   ██║██║  ███╗██████╔╝   ██║   ██║  ██║██║   ██║██║
██║╚██╗██║██╔══██║██║╚██╗██║██║   ██║██║   ██║██╔══██╗   ██║   ██║  ██║██║   ██║██║
██║ ╚████║██║  ██║██║ ╚████║╚██████╔╝╚██████╔╝██║  ██║   ██║   ██████╔╝╚██████╔╝███████╗
╚═╝  ╚═══╝╚═╝  ╚═╝╚═╝  ╚═══╝ ╚═════╝  ╚═════╝ ╚═╝  ╚═╝   ╚═╝   ╚═════╝  ╚═════╝ ╚══════╝

        ███████╗ ██████╗ ███████╗██╗     ██╗      ██████╗ ██╗   ██╗
        ██╔════╝██╔═══██╗██╔════╝██║     ██║     ██╔═══██╗╚██╗ ██╔╝
        █████╗  ██║   ██║█████╗  ██║     ██║     ██║   ██║ ╚████╔╝
        ██╔══╝  ██║   ██║██╔══╝  ██║     ██║     ██║   ██║  ╚██╔╝
        ██║     ╚██████╔╝██║     ███████╗███████╗╚██████╔╝   ██║
        ╚═╝      ╚═════╝ ╚═╝     ╚══════╝╚══════╝ ╚═════╝    ╚═╝
```

<h3>⚡ Ultra-Compact 32-bit Control Platform for Embedded & IoT Applications</h3>
<h4><i>Small footprint. Full control. Zero compromise.</i></h4>

<br/>

<br/>

---

**[📡 Overview](#-overview) · [✨ Features](#-features) · [🔩 Architecture](#-system-architecture) · [📐 Pinout](#-pinout-map) · [📦 BOM](#-bill-of-materials) · [🚀 Quickstart](#-quickstart) · [📁 File Tree](#-file-tree) · [🗺 Roadmap](#-roadmap) · [🤝 Contribute](#-contributing)**

---

</div>

<br/>

## 📡 Overview

**NanoControl F031 Platform** is a precision-engineered, ultra-compact 32-bit microcontroller platform built around the **STM32F031K6T6** — a cost-optimized ARM Cortex-M0+ MCU running at 48 MHz with 32 KB Flash and 4 KB SRAM. Designed for space-constrained embedded control, sensor interfacing, motor drive, and IoT edge nodes, NanoControl delivers full 32-bit processing power in a 32-pin LQFP footprint smaller than a postage stamp.

Engineered for rapid prototyping and production deployment alike, the platform features a hardened power architecture, crystal-accurate clocking, and a rich peripheral set — 12-bit ADC, multiple timers, I²C, SPI, USART, and PWM — all accessible through a clean, breadboard-friendly pinout.

```
NanoControl F031 Design Philosophy
───────────────────────────────────
  → 32-bit ARM performance in 8-bit footprint      (Cortex-M0+, 48 MHz)
  → Crystal-locked precision timing                (HSE 8 MHz + PLL)
  → EMI-hardened power delivery                    (ferrite + bulk caps)
  → Full peripheral coverage                       (ADC, PWM, I²C, SPI, UART)
  → Breadboard & PCB-ready pinout                  (2.54mm header spacing)
  → SWD debug + UART bootload                      (ST-Link / serial flash)
  → Ultra-low sleep modes                          (Stop / Standby < 10 µA)
```

<br/>

---

## ✨ Features

<br/>

<table>
<tr>
<td width="50%">

### 🧠 Processing & Memory
- **ARM Cortex-M0+** core @ 48 MHz (0.95 DMIPS/MHz)
- **32 KB Flash** — ample for complex control firmware
- **4 KB SRAM** — stack, heap, and runtime buffers
- **Hardware multiplier** — single-cycle 32×32 MAC
- **SysTick timer** — RTOS-ready tick generation
- **Nested Vectored Interrupt Controller** — 32 IRQ lines

</td>
<td width="50%">

### ⚡ Power & Clock
- **HSE 8 MHz crystal** — PLL-multiplied to 48 MHz system clock
- **Internal HSI 8 MHz RC** — fallback / fast boot clock
- **HSI14 14 MHz RC** — dedicated ADC asynchronous clock
- **Low-power modes**: Sleep, Stop, Standby (< 10 µA standby)
- **POR / PDR / BOR** — brown-out reset protection
- **Independent watchdog (IWDG)** — safety-critical recovery

</td>
</tr>
<tr>
<td width="50%">

### 🔌 Communication Peripherals
- **USART1** — Full-duplex UART with hardware flow control
- **SPI1** — Master/slave up to 24 Mbit/s
- **I²C1** — Fast-mode 400 kHz, SMBus support
- **CAN bus ready** — external transceiver via SPI bridge
- **SWD debug** — 2-wire Serial Wire Debug (PA13/PA14)

</td>
<td width="50%">

### 🎛️ Analog & Control
- **12-bit SAR ADC** — 10 channels, 1.0 µs conversion
- **9-channel PWM** — advanced motor / LED control
- **5× 16-bit timers** — TIM1 (advanced), TIM2, TIM3, TIM14, TIM16, TIM17
- **RTC** — 32-bit counter with alarm, calendar mode
- **GPIO** — 26 multi-function I/O lines, 5V-tolerant inputs

</td>
</tr>
</table>

<br/>

---

## 🔩 System Architecture

```
╔═══════════════════════════════════════════════════════════════════════════╗
║              NanoControl F031 — Full System Block Diagram                ║
╠═══════════════════════════════════════════════════════════════════════════╣
║                                                                           ║
║   ┌─────────────────────────────────────────────────────────────────┐     ║
║   │              STM32F031K6T6 — ARM Cortex-M0+ Core               │     ║
║   │                                                                 │     ║
║   │   ┌─────────────┐  ┌─────────────┐  ┌─────────────────────┐ │     ║
║   │   │  32 KB Flash │  │   4 KB SRAM  │  │  NVIC + SysTick     │ │     ║
║   │   │  (0x08000000)│  │  (0x20000000)│  │  32 IRQ priorities  │ │     ║
║   │   └─────────────┘  └─────────────┘  └─────────────────────┘ │     ║
║   │                                                                 │     ║
║   │   ┌─────────────┐  ┌─────────────┐  ┌─────────────────────┐ │     ║
║   │   │   RCC/PLL   │  │    PWR/BOR   │  │   Flash Prefetch    │ │     ║
║   │   │  48 MHz SYS │  │   LDO 1.8V   │  │   + 2 wait states   │ │     ║
║   │   └─────────────┘  └─────────────┘  └─────────────────────┘ │     ║
║   └────────────────────────┬────────────────────────────────────┘     ║
║                            │                                            ║
║   ════════════════════════ Peripherals ═════════════════════════════   ║
║                            │                                            ║
║   ┌──────────┐ ┌──────────┐ ┌──────────┐ ┌──────────┐ ┌──────────┐     ║
║   │  USART1  │ │  SPI1    │ │  I²C1    │ │  TIM1/2  │ │  ADC1    │     ║
║   │ PA9/PA10 │ │ PA5-PA7  │ │ PA9/PA10 │ │ PA0-PA3  │ │ PA0-PA7  │     ║
║   │ 115200   │ │ 24 Mbit  │ │ 400 kHz  │ │  PWM     │ │ 12-bit   │     ║
║   └──────────┘ └──────────┘ └──────────┘ └──────────┘ └──────────┘     ║
║                            │                                            ║
║   ════════════════════════ Clock Tree ══════════════════════════════   ║
║                            │                                            ║
║        ┌───────────────────┴───────────────────┐                        ║
║        ▼                                       ▼                        ║
║   ┌─────────┐    ┌─────────┐    ┌─────────┐    ┌─────────┐            ║
║   │  HSE    │───▶│  PLL    │───▶│ SYSCLK  │───▶│ AHB/HCLK│  48 MHz     ║
║   │ 8 MHz   │    │ ×6      │    │ 48 MHz  │    │         │             ║
║   │  Y1     │    │         │    │         │    │ APB     │  48 MHz     ║
║   └─────────┘    └─────────┘    └─────────┘    └─────────┘            ║
║        │                                       │                        ║
║        └───────────────────┬───────────────────┘                        ║
║                            ▼                                            ║
║                       ┌─────────┐                                        ║
║                       │  HSI14  │───▶ ADC async clock (14 MHz)          ║
║                       │ 14 MHz  │                                        ║
║                       └─────────┘                                        ║
║                                                                           ║
║   ════════════════════════ Power Rail ════════════════════════════════   ║
║                                                                           ║
║   VIN (5V) → LDO 3.3V → FB1 (ferrite) → VDD ──┬── C9/C10 bulk (10µF)   ║
║                                                 └── C1–C8 decoupling     ║
║                                                                           ║
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
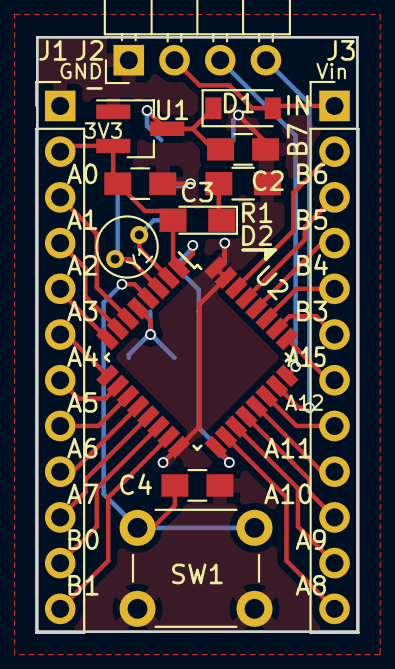
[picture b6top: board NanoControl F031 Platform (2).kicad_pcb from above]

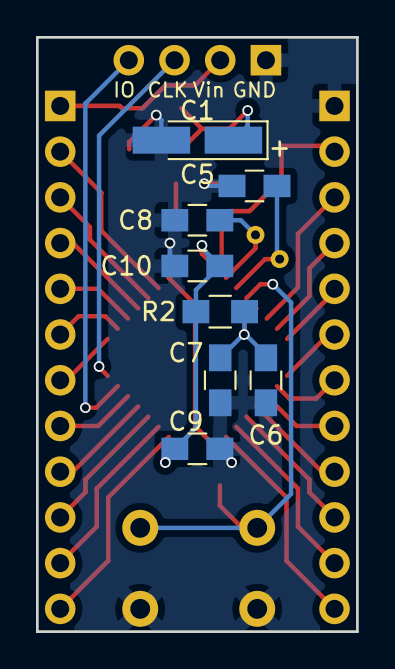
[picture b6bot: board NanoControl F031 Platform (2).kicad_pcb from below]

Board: 2 copper layers, 17.8 x 33.0 mm, 21 parts (8 on the bottom side), 32 nets.

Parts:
C1: 10uF; CP_Tantalum_Case-A_EIA-3216-18_Hand
C2, C3: 4.7uF; C_0805_HandSoldering
C4, C9, C10: 100nF; C_0805_HandSoldering
C5, C8: 20pF; C_0805_HandSoldering
C6: 10nF; C_0805_HandSoldering
C7: 1uF; C_0805_HandSoldering
D1: Schottky; D_SOD-123
D2: Power_On?; LED_0805_HandSoldering
J1: GPIO1; Pin_Header_Straight_1x12_Pitch2.54mm
J2: Prog; Pin_Header_Angled_1x04_Pitch2.54mm
J3: GPIO2; Pin_Header_Straight_1x12_Pitch2.54mm
R1: RLED; R_0805_HandSoldering
R2: FBead; R_0805_HandSoldering
SW1: Reset; SW_PUSH_6mm
U1: AP2210; SOT-23_Handsoldering
U2: STM32F031K6; LQFP-32_7x7mm_Pitch0.8mm
Y1: 8MHz; Crystal_Round_d3.0mm_Vertical

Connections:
+3V3: C3.1, C9.2, C10.1, D2.2, J1.2, R2.2, U1.2, U2.1, U2.17
A0: J1.3, U2.6
A1: J1.4, U2.7
A2: J1.5, U2.8
A3: J1.6, U2.9
A4: J1.7, U2.10
A5: J1.8, U2.11
A6: J1.9, U2.12
A7: J1.10, U2.13
A8: J3.12, U2.18
A9: J3.11, U2.19
A10: J3.10, U2.20
A11: J3.9, U2.21
A12: J3.8, U2.22
A15: J3.7, U2.25
B0: J1.11, U2.14
B1: J1.12, U2.15
B3: J3.6, U2.26
B4: J3.5, U2.27
B5: J3.4, U2.28
B6: J3.3, U2.29
B7: J3.2, U2.30
GND: C1.2, C2.2, C3.2, C4.2, C5.1, C6.2, C7.2, C8.1, C9.1, C10.2, J1.1, J2.1, R1.2, SW1.1, U1.1, U2.16, U2.31, U2.32
unnamed: C1.1, C2.1, D1.1, U1.3
unnamed: C4.1, SW1.2, U2.4
unnamed: C5.2, U2.3, Y1.1
unnamed: C6.1, C7.1, R2.1, U2.5
unnamed: C8.2, U2.2, Y1.2
unnamed: D2.1, R1.1
SWCLK: J2.3, U2.24
SWDIO: J2.4, U2.23
VPP: D1.2, J2.2, J3.1

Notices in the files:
EmbedMatrix/README.md:
📜 License:
MIT License
Copyright (c) 2025 Mahesh Thilak K
Permission is hereby granted, free of charge, to any person obtaining
a copy of this hardware design, firmware, and associated documentation,
to use, copy, modify, merge, publish, distribute, sublicense, and/or
sell copies — subject to the above copyright notice appearing in all
copies or substantial portions.
THE HARDWARE AND FIRMWARE ARE PROVIDED "AS IS", WITHOUT WARRANTY.
Full text: [LICENSE](LICENSE)
License: MIT
║ © 2025 Mahesh Thilak K — MIT ║
